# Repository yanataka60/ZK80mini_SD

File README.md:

# ZK80mini_SD
　Katsumiさんが公開してくださっている素晴らしいNEC TK-80互換機 ZK-80miniにSDカードによるLOAD、SAVEとスピーカーを載せてみました。

　　KZ-80mini

　　　　http://www.recfor.net/blog/mycom/index.php?itemid=883

　SDカードのアクセスには、ケンケンさんが公開してくださっているSDカードアクセスライブラリを用いています。

　　SDカードアクセスライブラリ

　　　　http://www.ze.em-net.ne.jp/~kenken/bootloader/index.html

## 回路図

## 部品表
|番号|品名|数量|備考|
| ------------ | ------------ | ------------ | ------------ |
|U1|4桁7セグメントLED アノードコモン アノード共通接続|1|秋月電子通商 OSL40562-IRA|
|U2|4桁7セグメントLED カソードコモン カソード共通接続|1|秋月電子通商 OSL40562-LRA|
|U3|PIC32MX150F128B|1|マルツオンライン等|
|U4|低消費電力LDO 7333-A|1|オレンジピコショップ 秋月電子通商 S-812C33AY-B-Gでも可|
|J1|6Pinコネクタ|1||
|J2|Micro SD Card Kit|1|秋月電子通商 AE-MICRO-SD-DIP|
|J3|マイクロUSBコネクタ 電源供給用|1|秋月電子通商 MRUSB-2B-D14NI-S306|
|J4|14P(2×7P) コネクタ|1|ケーブルで繋ぐならボックスヘッダー、直差しするならピンソケット|
|S1 S2|3Pスライドスイッチ|2||
|R1|カーボン抵抗 1/6W 330Ω|1||
|R2 R3 R4 R5|カーボン抵抗 1/6W 100Ω|4||
|R6 R7 R8 R9|カーボン抵抗 1/6W 10kΩ|4||
|C1|電解コンデンサ 16v10μF|1||
|C2 C3 C4|積層セラミックコンデンサ 0.1μF|3||
|C5 C6|積層セラミックコンデンサ 10μF|2||
|LS1|圧電スピーカー(圧電サウンダ)(13mm)|1|秋月電子通商 PKM13EPYH4000-A0|
||キーボード|1|オレンジピコショップ ZK-80-KB 組立てキット|

## その他必要なもの
|品名|
| ------------ |
|Microchip社のPICマイコン書き込み機 PICKit3等|

## PIC書き込み環境
|名称	|
| ------------ |
|MPLAB X IDE|
|MPLAB XC32compiler V1.21|

## PICへの書き込み
　MPLABフォルダに２通りのコンパイル済みバイナリを用意しています。

　　zk80mini_8080.hex(CPU 8080)

　　zk80mini_z80.hex(CPU Z80)

　このバイナリを使うのであればMPLAB X IDE付属のMPLAB X IPEにより書き込んでください。

　コンパイルしたい方はMPLAB/zk80mini_SDフォルダのプロジェクトをMPLAB X IDEでコンパイルして書き込んでください。

## バイナリに含まれるTK-80互換モニタープログラムについて
　ZK80miniオリジナルに含まれるTK-80互換モニタープログラムをそのまま使用しています。

　詳しくはオリジナルのreadme.txtを参照してください。

## 使い方
　使い方の基本はTK-80と同様です。

　ROM $0000-$02FF(768Byte)

　RAM $8000-$F1FF(28KByte)

　SDカードのファイルシステムは、FAT32対応ですが、8.3形式のファイル名のみ使用可です。

　本システムでのファイルネームは16進数4桁のファイルNoに3文字の拡張子です。

　スピーカーは、TK-80 8255 PC1に接続をエミュレートしています。

　　注)互換モニターでSDカードからのロード直後にRUNキーで実行すると音が出ない場合があるようです。その時には一回RESETを押し、ADRS SETをし直してRUNしてください。

　　　なお、rom.hをTK-80正規モニターに差し替えてコンパイルすれば音の出ない不具合は解消されます。

　また、ICSPに繋ぐピンをLED、キーボードと兼用していますのでPICKit3をICSPに接続したままキーボード操作をすると誤動作します。(2、7、LOAD DATAのキーが効きません。書き込みは正常に行えます。)

#### TK-80正規モニターに差し替える場合は、TK-80正規モニターに以下の修正を加えて差し替えてください。
00D5: AF　　　　　　XOR　A

00D6: D3 9E 　　　　OUT　(9Eh),A

00D8: CD A1 01　　　CALL　01A1h

00DB: C3 51 00　　　JP　0051h

0107: 3E 01 　　　　LD　A,01h

0109: D3 9E 　　　　OUT　(9Eh),A

010B: CD A1 01　　　CALL　01A1h

010E: C3 51 00　　　JP　0051h

## SAVE
　ファイルNo(xxxx)を8000～FFFFの16進数4桁で入力して「STORE DATA」キーを押します。

　メモリ 8000h～F1FFhまでをxxxx.ZK8としてセーブします。セーブ範囲は固定となっていて指定はできません。

　SDカードには、ファイルNo(xxxx).ZK8という名前で保存されます。

　SDカードに同じファイルNoのZK8ファイルがあった場合には上書きされます。

　ファイルNo、0000～7FFFまでは上書きによる消失を防ぐため読み出し専用のファイルNoになっています。

　ファイルNo、8000～FFFFは読み書き自由です。

　ZK8形式は、ヘッダ情報等が付加されていないファイル長28,672Byteのベタなバイナリファイルです。

## LOAD
　ファイルNo(xxxx)を0000～FFFFの16進数4桁で入力して「LOAD DATA」キーを押します。

　正常にLOADされた場合は、LED ADDRESS表示部にLOAD開始アドレス、LED DATA表示部にLOAD終了アドレスが表示されます。

　LOADするファイルの拡張子はZK8、TK8、BIN、BTK、HEXに対応しており、違う拡張子で同じファイルNoのファイルがSDカードに保存されていた場合には次の順に検索されます。

　　　検索順：ZK8 -> TK8 -> BIN -> BTK -> HEX

### ZK8、TK8、BIN
　すべて、ヘッダ情報等が付加されていないベタなバイナリファイル。

　SDカードから読み込まれたファイルはメモリの8000hからファイル長分LOADされます。

　ただし、メモリへの書き込みアドレスが83B0h～83D0h、83E0h～83FFh、F200h～FFFFHまでの範囲の読み出しデータはメモリに書き込まれません。

### BTK
　バイナリファイル本体データの先頭に2Byteの開始アドレス、2Byteの終了アドレス合計4Byteを付加した形になっているファイル。

　SDカードから読み込まれたファイルは開始アドレスから終了アドレスまでLOADされます。

　ただし、メモリへの書き込みアドレスが83B0h～83D0h、83E0h～83FFh、F200h～FFFFHまでの範囲の読み出しデータはメモリに書き込まれません。

### HEX
　インテルHEX形式のファイル。

　SDカードから読み込まれたファイルはインテルHEX形式に基づいてLOADされます。

　ただし、メモリへの書き込みアドレスが83B0h～83D0h、83E0h～83FFh、F200h～FFFFHまでの範囲の読み出しデータはメモリに書き込まれません。

### 注意
　SDカードにアクセスしていなければ電源ON時でもSDカードの抜き差しは可能ですが、再挿入後にはZK80miniをリセットしてください。

## 免責事項
　このツールを参考にして行った事による、いかなる不具合に関しても、私は責任を持ちません。各自、自己責任のもとで作業を行ってください。

## 著作権について
　KUT KiCad Connector footprint libraryは、The MIT License (MIT)。

　SDカードライブラリのlibsdfsio.a、SDFSIO.hについては、ケンケンさんが公開しているMicrochip社のライブラリを利用。(SDFSIO.hにライセンスの記載在り)

　それ以外は、ZK-80miniのライセンスと同様にすべてLGPL v2.0の元配布します。

## 謝辞
　ZK80miniを公開してくださったKatsumi様

　SDカードアクセスライブラリを公開してくださったケンケン様

　ありがとうございました。

## 追記
2022.5.5

         LOAD除外範囲を修正、著作権表記を修正。

         部品表 J2 Micro SD Card Kitの品番を修正。

         コメントを追加したところ、コンパイル後、動作が不安定になることがあるためコメント一部削除

2022.5.6

         コメント再追加

         SDカードからLOAD直後にスピーカーから音が出ない場合への対処を付記。

2022.5.11

         TK-80正規モニターに差し替える場合の修正点を追記。

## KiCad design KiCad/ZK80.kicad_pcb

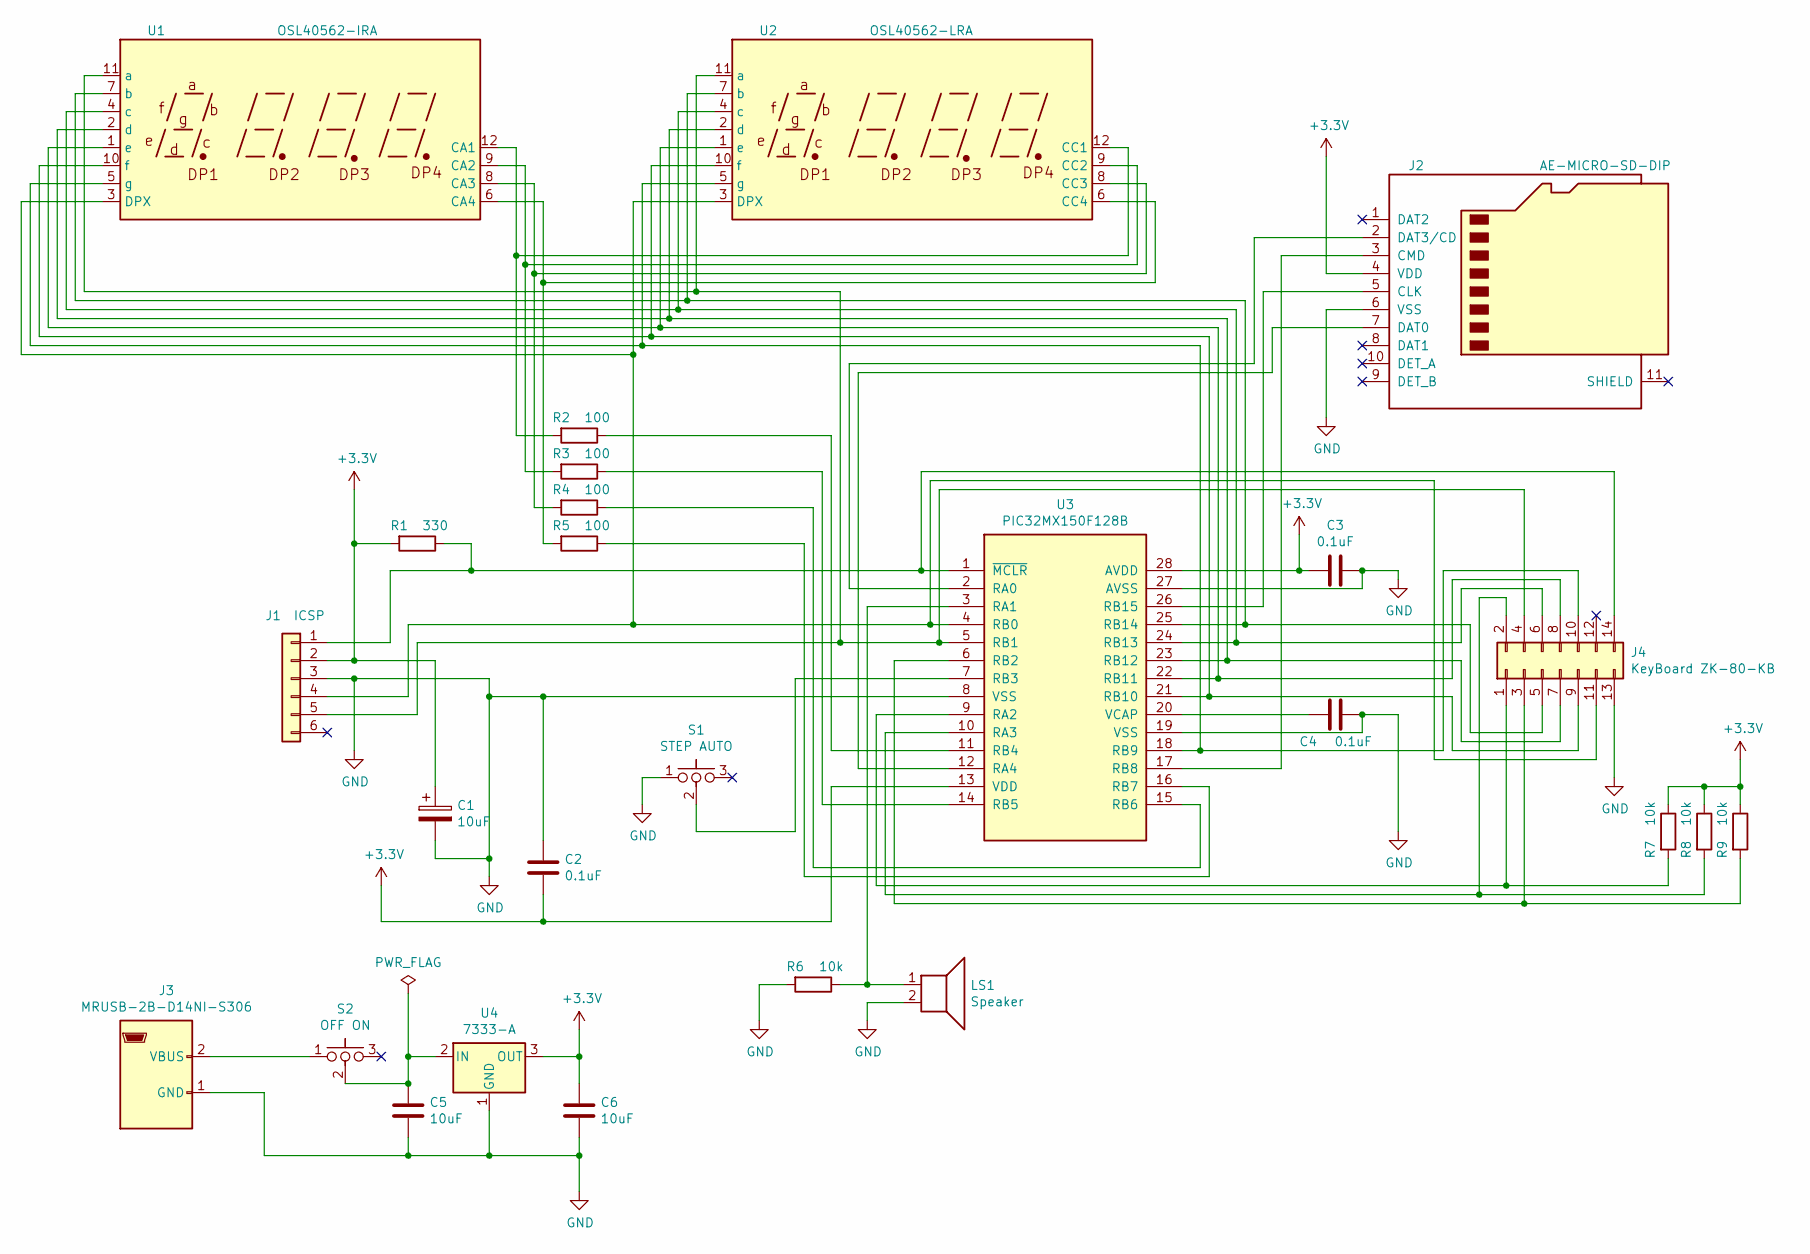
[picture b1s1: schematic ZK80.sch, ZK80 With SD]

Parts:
C1: 10uF; CP_Radial_D5.0mm_P2.50mm
C2, C3, C4: 0.1uF; C_Rect_L4.0mm_W2.5mm_P2.50mm
C5, C6: 10uF; C_Rect_L4.0mm_W2.5mm_P2.50mm
J1: ICSP; PinHeader_1x06_P2.54mm_Horizontal
J2: AE-MICRO-SD-DIP
J3: MRUSB-2B-D14NI-S306
J4: KeyBoard ZK-80-KB; PinHeader_2x07_P2.54mm_Vertical
LS1: Speaker; TO-5-2
R1: 330; R_Axial_DIN0207_L6.3mm_D2.5mm_P7.62mm_Horizontal
R2, R3, R4, R5: 100; R_Axial_DIN0207_L6.3mm_D2.5mm_P7.62mm_Horizontal
R6, R7, R8, R9: 10k; R_Axial_DIN0207_L6.3mm_D2.5mm_P7.62mm_Horizontal
S1: STEP AUTO; PinHeader_1x03_P2.54mm_Vertical
S2: OFF ON; PinHeader_1x03_P2.54mm_Vertical
U1: OSL40562-IRA; CA56-12EWA
U2: OSL40562-LRA; CA56-12EWA
U3: PIC32MX150F128B; DIP-28_W7.62mm_LongPads
U4: 7333-A; TO-92_Inline_Wide

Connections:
+3V3: C1.1, C2.2, C3.1, C6.1, J1.2, J2.4 (VDD), R1.2, R7.1, R8.1, R9.1, U3.13 (VDD), U3.28 (AVDD), U4.3 (OUT)
GND: C1.2, C2.1, C3.2, C4.2, C5.2, C6.2, J1.3, J2.6 (VSS), J3.1 (GND), J4.13, LS1.2, R6.2, S1.1, U3.8 (VSS), U3.19 (VSS), U3.27 (AVSS), U4.1 (GND)
unnamed: C4.1, U3.20 (VCAP)
unnamed: C5.1, S2.2, U4.2 (IN)
unnamed: J1.1, J4.14, R1.1, U3.1 (~MCLR)
unnamed: J1.4, J4.11, U1.3 (DPX), U2.3 (DPX), U3.4 (RB0)
unnamed: J1.5, J4.4, U1.11 (a), U2.11 (a), U3.5 (RB1)
unnamed: J2.2 (DAT3/CD), U3.2 (RA0)
unnamed: J2.3 (CMD), U3.17 (RB8)
unnamed: J2.5 (CLK), U3.26 (RB15)
unnamed: J2.7 (DAT0), U3.12 (RA4)
unnamed: J3.2 (VBUS), S2.1
unnamed: J4.1, R7.2, U3.9 (RA2)
unnamed: J4.2, R8.2, U3.10 (RA3)
unnamed: J4.3, R9.2, U3.6 (RB2)
unnamed: J4.5, U1.7 (b), U2.7 (b), U3.25 (RB14)
unnamed: J4.6, U1.4 (c), U2.4 (c), U3.24 (RB13)
unnamed: J4.7, U1.2 (d), U2.2 (d), U3.23 (RB12)
unnamed: J4.8, U1.1 (e), U2.1 (e), U3.22 (RB11)
unnamed: J4.9, U1.10 (f), U2.10 (f), U3.21 (RB10)
unnamed: J4.10, U1.5 (g), U2.5 (g), U3.18 (RB9)
unnamed: LS1.1, R6.1, U3.3 (RA1)
unnamed: R2.1, U3.11 (RB4)
unnamed: R2.2, U1.12 (CA1), U2.12 (CC1)
unnamed: R3.1, U3.14 (RB5)
unnamed: R3.2, U1.9 (CA2), U2.9 (CC2)
unnamed: R4.1, U3.15 (RB6)
unnamed: R4.2, U1.8 (CA3), U2.8 (CC3)
unnamed: R5.1, U3.16 (RB7)
unnamed: R5.2, U1.6 (CA4), U2.6 (CC4)
unnamed: S1.2, U3.7 (RB3)

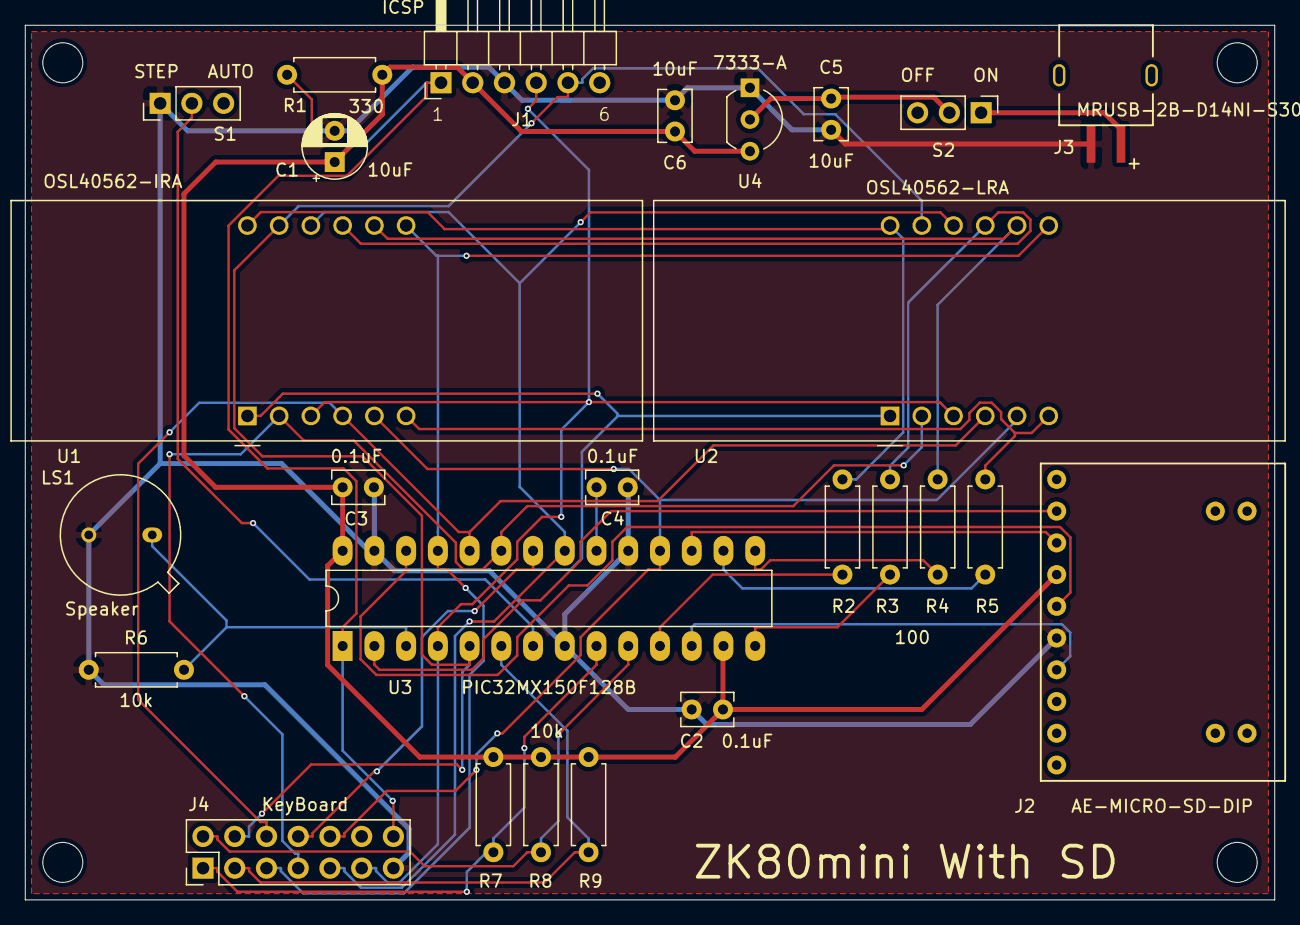
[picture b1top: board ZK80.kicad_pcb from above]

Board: 2 copper layers, 100.0 x 70.0 mm, 30 parts (0 on the bottom side), 31 nets.

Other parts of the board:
MH1, MH2, MH3, MH4: MountingHole_3.2mm_M3
